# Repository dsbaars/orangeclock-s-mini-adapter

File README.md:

# Orangeclock S* mini to EPD adapter

## Pins S2 mini

```
RST_PIN         = 3
DC_PIN          = 2
CS_PIN          = 4
BUSY_PIN        = 1
```

## Pins S3 mini

```
RST_PIN         = 2
DC_PIN          = 3
CS_PIN          = 5
BUSY_PIN        = 1
```

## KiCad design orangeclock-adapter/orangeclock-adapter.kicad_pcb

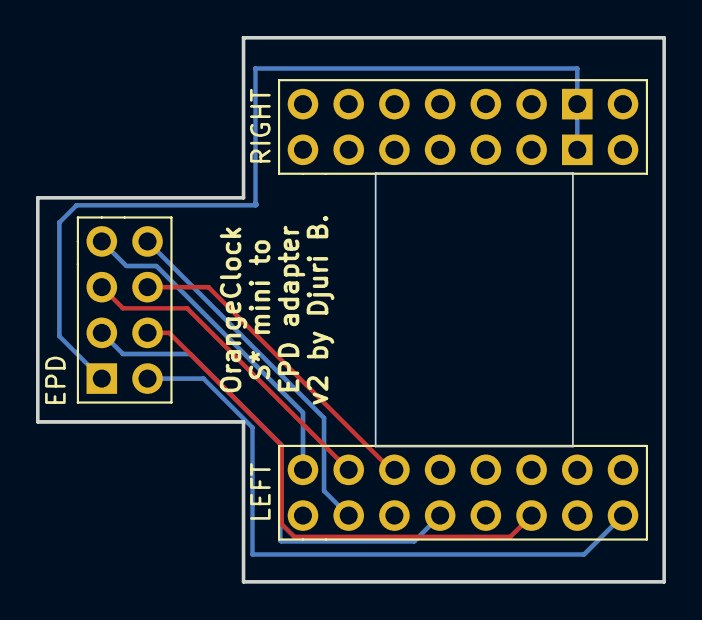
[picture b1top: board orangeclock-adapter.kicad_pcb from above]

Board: 2 copper layers, 34.8 x 30.2 mm, 3 parts (0 on the bottom side), 8 nets.

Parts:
J1: EPD; PinHeader_2x04_P2.54mm_Vertical
LEFT: Conn_02x08_Odd_Even; PinHeader_2x08_P2.54mm_Vertical
RIGHT: Conn_02x08_Odd_Even; PinHeader_2x08_P2.54mm_Vertical_nognd

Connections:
+3V3: J1.8, LEFT.15
BUSY: J1.1, LEFT.2
CS: J1.4, LEFT.6
DC: J1.3, LEFT.4
GND: J1.7, RIGHT.13, RIGHT.14
RES: J1.2, LEFT.3
SCL: J1.5, LEFT.7
SDA: J1.6, LEFT.11
